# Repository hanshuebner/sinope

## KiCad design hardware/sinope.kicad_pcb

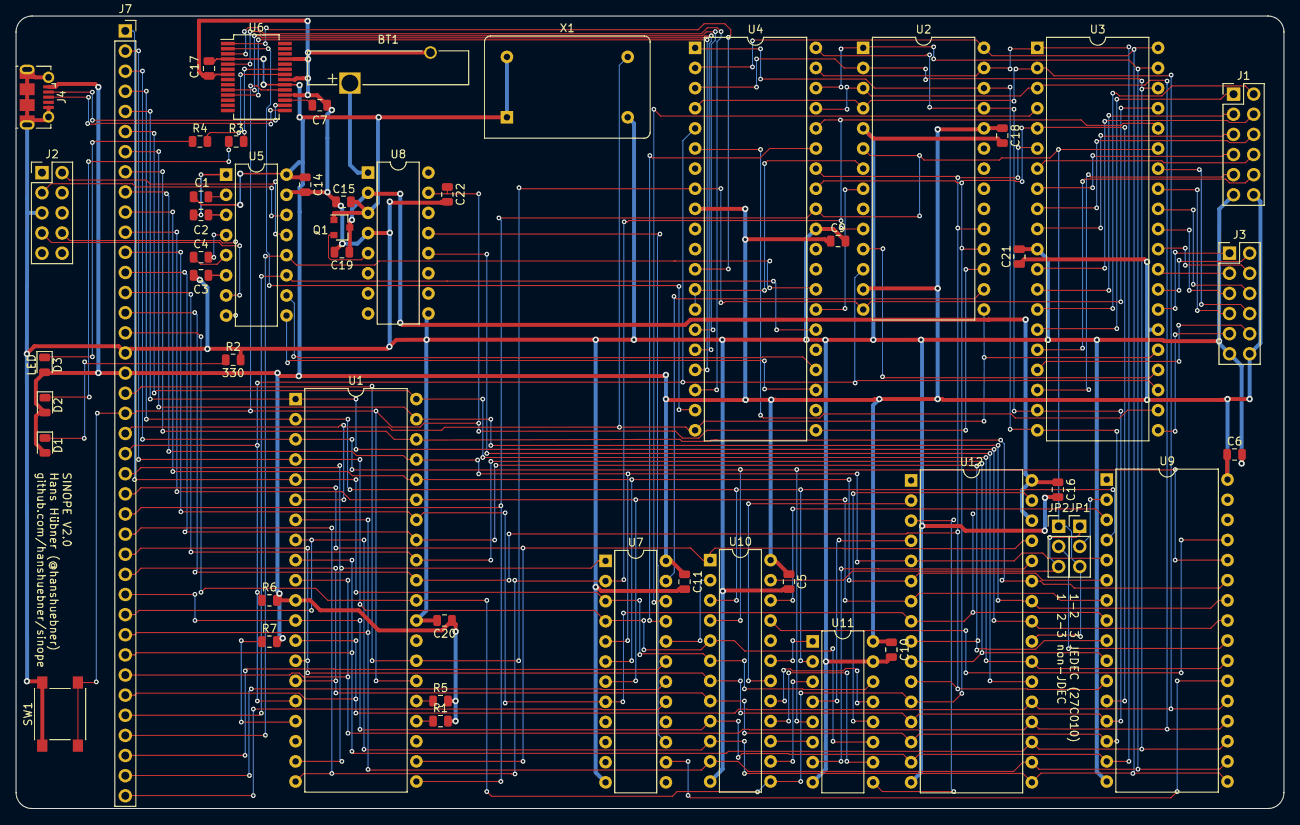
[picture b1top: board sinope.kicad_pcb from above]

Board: 2 copper layers, 160.0 x 100.0 mm, 52 parts (0 on the bottom side), 117 nets.

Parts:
BT1: Battery; Battery_Panasonic_CR2032-VS1N_Vertical_CircularHoles
C1, C2, C3, C4, C5, C6, C7, C9, C10, C11, C14, C15, C16, C17, C18, C19, C20, C21, C22: 100nF; C_0805_2012Metric
D1, D2, D3: LED; LED_0805_2012Metric
J1: PIOA; PinHeader_2x06_P2.54mm_Vertical
J2: SERIAL1; PinHeader_2x05_P2.54mm_Vertical
J3: PIOB; PinHeader_2x06_P2.54mm_Vertical
J4: USB_B_Micro; USB_Micro-B_Molex-105017-0001
J7: Z80_BUS; PinSocket_1x39_P2.54mm_Vertical
JP1, JP2: SolderJumper_3_Bridged12; PinHeader_1x03_P2.54mm_Vertical
Q1: MMBT3904; SOT-23
R1, R5, R6, R7: 3k3; R_0805_2012Metric
R2, R3, R4: 330; R_0805_2012Metric
SW1: RESET; SW_SPST_PTS645
U1: Z80CPU; DIP-40_W15.24mm
U2: Z80CTC; DIP-28_W15.24mm
U3: Z80PIO; DIP-40_W15.24mm
U4: Z80SIO; DIP-40_W15.24mm
U5: MAX232; DIP-16_W7.62mm
U6: FT232RL; SSOP-28_5.3x10.2mm_P0.65mm
U7: IO_GAL; DIP-24_W7.62mm
U8: MAX695; DIP-16_W7.62mm
U9: 27C010; DIP-32_W15.24mm
U10: MEMORY_GAL; DIP-24_W7.62mm
U11: 74LS157; DIP-16_W7.62mm
U12: TC551001; DIP-32_W15.24mm
X1: 3.6864Mhz; Oscillator_DIP-14

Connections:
+5V: C1.2, C5.1, C6.1, C9.1, C10.1, C11.1, C14.1, C15.1, C17.1, C18.1, C20.1, C21.1, D1.2, D2.2, D3.2, J1.12, J3.12, J4.1, J7.18, Q1.1, R1.2, R5.2, R6.2, R7.2, U1.11, U2.13, U2.24, U3.26, U4.9, U5.16, U6.4, U6.20, U7.24, U8.3, U9.32, U10.24, U11.16, X1.1, X1.14
/A0: J7.16, U1.30, U2.18, U3.5, U4.33, U9.12, U10.13, U12.12
/A1: J7.15, U1.31, U2.19, U3.6, U4.34, U9.11, U12.11
/A2: J7.14, U1.32, U9.10, U12.10
/A3: J7.13, U1.33, U9.9, U12.9
/A4: J7.12, U1.34, U7.8, U9.8, U12.8
/A5: J7.11, U1.35, U7.7, U9.7, U12.7
/A6: J7.10, U1.36, U7.6, U9.6, U12.6
/A7: J7.9, U1.37, U7.5, U9.5, U12.5
/A8: J7.8, U1.38, U9.27, U12.27
/A9: J7.7, U1.39, U9.26, U12.26
/A10: J7.6, U1.40, U9.23, U12.23
/A11: J7.5, U1.1, U9.25, U12.25
/A12: J7.4, U1.2, U9.4, U10.3, U11.2
/A13: J7.3, U1.3, U9.28, U10.4, U11.5
/A14: J7.2, U1.4, U7.4, U10.5, U11.11
/A15: J7.1, U1.5, U7.3, U10.6, U11.14
/D0: J7.27, U1.14, U2.25, U3.19, U4.40, U9.13, U10.7, U12.13
/D1: J7.28, U1.15, U2.26, U3.20, U4.1, U9.14, U10.8, U12.14
/D2: J7.29, U1.12, U2.27, U3.1, U4.39, U9.15, U10.9, U12.15
/D3: J7.30, U1.8, U2.28, U3.40, U4.2, U9.17, U10.10, U12.17
/D4: J7.31, U1.7, U2.1, U3.39, U4.38, U9.18, U10.11, U12.18
/D5: J7.32, U1.9, U2.2, U3.38, U4.3, U9.19, U12.19
/D6: J7.33, U1.10, U2.3, U3.3, U4.37, U9.20, U12.20
/D7: J7.34, U1.13, U2.4, U3.2, U4.4, U9.21, U12.21
/ROMA14: U9.29, U10.21
/ROMA15: U9.3, U10.22
/ROMA16: JP1.1, JP2.3, U10.23
CLK: J7.21, U1.6, U2.15, U3.25, U4.20, X1.8
GND: BT1.2, C3.1, C5.2, C6.2, C7.2, C9.2, C10.2, C11.2, C14.2, C15.2, C16.2, C17.2, C18.2, C19.2, C20.2, C21.2, C22.2, J1.11, J2.5, J3.11, J4.5, J4.6, J7.17, R2.2, SW1.1, U1.29, U2.5, U3.11, U4.31, U5.15, U6.7, U6.18, U6.21, U6.25, U7.12, U8.4, U8.9, U9.16, U10.12, U11.8, U11.15, U12.16, X1.7
unnamed: BT1.1, U8.1
unnamed: C1.1, U5.2
unnamed: C2.1, U5.1
unnamed: C2.2, U5.3
unnamed: C3.2, U5.6
unnamed: C4.1, U5.5
unnamed: C4.2, U5.4
unnamed: C7.1, U6.17
unnamed: D1.1, R2.1
unnamed: D2.1, R3.1
unnamed: D3.1, R4.1
unnamed: J1.1, U3.15
unnamed: J1.2, U3.14
unnamed: J1.3, U3.13
unnamed: J1.4, U3.12
unnamed: J1.5, U3.10
unnamed: J1.6, U3.9
unnamed: J1.7, U3.8
unnamed: J1.8, U3.7
unnamed: J1.9, U3.18
unnamed: J1.10, U3.16
unnamed: J2.2, U5.13
unnamed: J2.3, U5.14
unnamed: J2.7, U5.7
unnamed: J2.8, U5.8
unnamed: J3.1, U3.27
unnamed: J3.2, U3.28
unnamed: J3.3, U3.29
unnamed: J3.4, U3.30
unnamed: J3.5, U3.31
unnamed: J3.6, U3.32
unnamed: J3.7, U3.33
unnamed: J3.8, U3.34
unnamed: J3.9, U3.21
unnamed: J3.10, U3.17
unnamed: JP1.2, U9.2
unnamed: JP2.2, U9.24
unnamed: Q1.2, U8.5
unnamed: R3.2, U6.23
unnamed: R4.2, U6.22
unnamed: U2.11, U3.24
unnamed: U3.22, U4.6
unnamed: U4.12, U6.1
unnamed: U4.15, U6.5
unnamed: U4.16, U6.10
unnamed: U4.17, U6.11
unnamed: U4.18, U6.3
unnamed: U4.19, U6.2
unnamed: U4.23, U5.9
unnamed: U4.24, U5.10
unnamed: U10.14, U11.3
unnamed: U10.15, U11.6
unnamed: U10.16, U11.10
unnamed: U10.17, U11.13
unnamed: U10.19, U11.1
unnamed: U11.4, U12.4
unnamed: U11.7, U12.28
unnamed: U11.9, U12.3
unnamed: U11.12, U12.31
RAMA16: U10.18, U12.2
RAMVCC: C16.1, C19.1, Q1.3, U8.2, U12.30, U12.32
RxDB: J7.36, U4.28, U5.12
SIOCA: U2.7, U4.13, U4.14
SIOCB: U2.8, U4.27
SPARE1: J7.37, U7.19
SPARE2: J7.38, U7.18
SPARE3: J7.39, U7.17
TxDB: J7.35, U4.26, U5.11
USB_D+: J4.3, U6.15
USB_D-: J4.2, U6.16
~BANKCS: U7.20, U10.2
~BUSRQ: R5.1, U1.25
~CTCCS: U2.16, U7.23
~INT: J7.22, R6.1, U1.16, U2.12, U3.23, U4.5
~IOREQ: J7.26, U1.20, U2.10, U3.36, U4.36, U7.2
~M1: J7.19, U1.27, U2.14, U3.37, U4.8
~MREQ: J7.23, U1.19, U7.1
~NMI: R7.1, U1.17
~PIOCS: U3.4, U7.22
~RAMCS: U7.15, U8.13
~RAMCS_SAFE: U8.12, U12.22
~RD: J7.25, JP1.3, JP2.1, U1.21, U2.6, U3.35, U4.32, U12.24
~RESET: C22.1, J7.20, SW1.2, U1.26, U2.17, U4.21, U6.19, U8.15
~ROMCS: U7.14, U9.22
~SIOCS: U4.35, U7.21
~WAIT: R1.1, U1.24
~WR: J7.24, U1.22, U10.1, U12.29

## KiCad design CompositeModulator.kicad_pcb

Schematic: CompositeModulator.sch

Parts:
C23, C44: 10uF
C24, C26: 10pF
C25, C28, C30, C34, C45: 1nF
C27: 150pF
C29: 13pF
C31: 47pF
C32: 100µF
C33: 56pF
C35, C37, C41: 100pF
C36: 7pF
C38, C40: 680pF
C39: 6-50pF
C42: 100nF; C_0805_2012Metric
C43: 390pF
L1, L2: 3.9µH
L3: 1.35-2.25µH
Q2: 9015
Q3: 9014
R3, R9, R10, R16, R21, R22: 560
R4: 47k
R5: 680
R6: 2.7k
R7: 820
R8: 5.6k
R11, R17: 10k
R12, R13, R18: 2.2k
R14: 220
R15: 270
R19, R20: 390
U13: TBA520
U14: 74LS04
Y1: 4.433618 Mhz

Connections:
+5V: C42.1, L2.1, Q2.1 (E), R11.1, R17.1, U13.6; also elsewhere on the board
GND: C25.2, C27.2, C28.2, C31.2, C32.2, C33.2, C34.2, C41.2, C42.2, C43.2, C44.2, C45.2, L3.2, R3.2, R4.2, R5.2, R9.2, R11.3, R13.2, R14.2, R16.2, R17.3, R19.2, U13.16; also elsewhere on the board
unnamed 2: C23.1, C25.1, L1.1, R3.1; also elsewhere on the board
unnamed: C23.2, Q2.2 (B), R4.1
unnamed: C24.1, U13.15
unnamed: C24.2, C26.2, Q2.3 (C), R5.1
unnamed: C26.1, U13.14
unnamed: C27.1, L1.2, R6.1
unnamed 8: C28.1, R7.2, R9.1; also elsewhere on the board
unnamed: C29.1, R10.2
unnamed: C29.2, C30.1, U13.5
unnamed: C30.2, C33.1, L3.1, R13.1
unnamed: C31.1, C32.1, L2.2, Q3.3, R8.1
unnamed 13: C34.1, C35.2, R15.2, R16.1; also elsewhere on the board
unnamed: C35.1, R15.1, R18.2, U13.13
unnamed: C36.1, C37.2, R20.2
unnamed: C36.2, C39.1, Y1.1
unnamed: C37.1, C38.2, R19.1
unnamed: C38.1, U13.2
unnamed: C39.2, C43.1, R21.2, U14.1
unnamed: C40.1, U13.8
unnamed: C40.2, C41.1, R20.1
unnamed: C44.1, R21.1, R22.2
unnamed: C45.1, R22.1, U14.2, Y1.2
unnamed 24: Q3.1, R14.1; also elsewhere on the board
unnamed: Q3.2, R6.2, R8.2, R10.1
unnamed: R11.2, R12.1
unnamed: R7.1, R12.2, U13.9
unnamed: R17.2, R18.1

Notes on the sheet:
(Q=100)
(Q=130)
This is a reproduction of the SVI328 video modulator circuitry
from http://www.samdal.com/SVIDOCS/STM-A_SVI328.pdf page 21

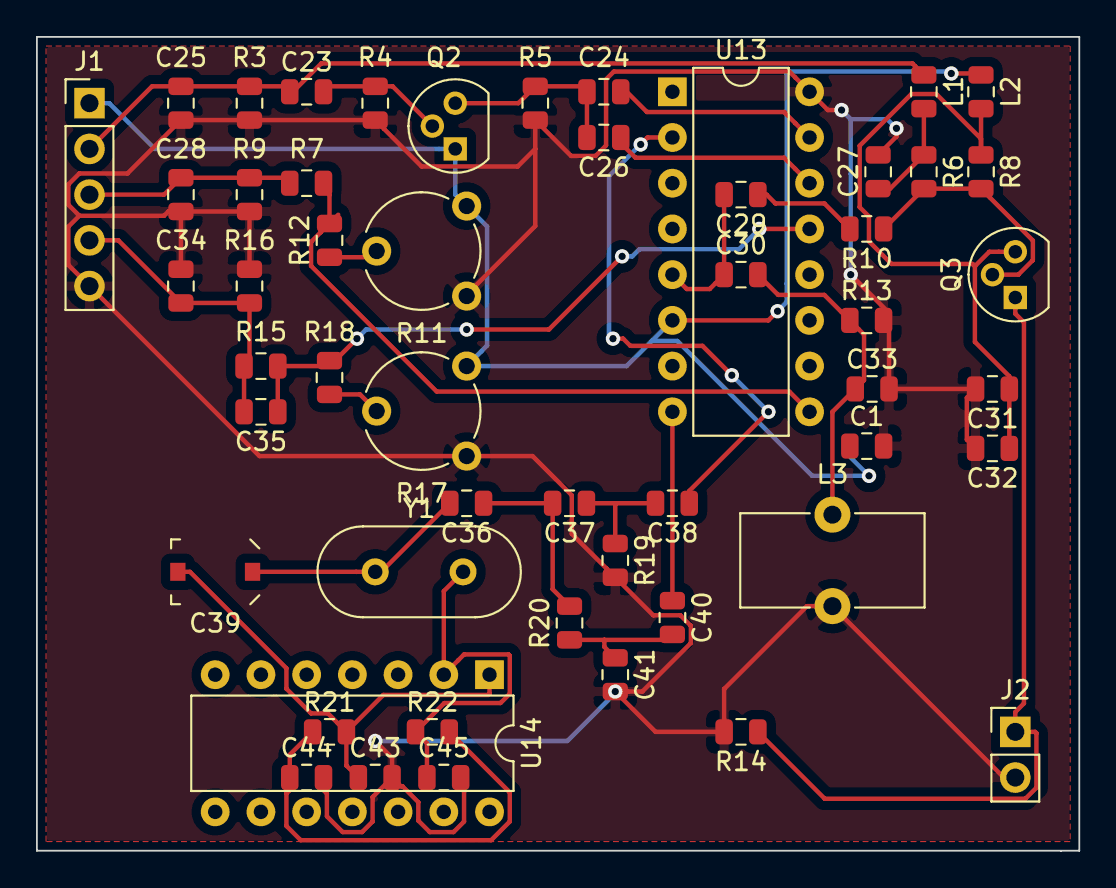
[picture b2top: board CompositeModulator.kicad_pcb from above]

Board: 2 copper layers, 57.9 x 45.2 mm, 53 parts (0 on the bottom side), 29 nets.

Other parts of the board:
C1: 100nF; C_0805_2012Metric
J1: Input; PinHeader_1x05_P2.54mm_Vertical
J2: Composite Video; PinHeader_1x02_P2.54mm_Vertical

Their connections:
+5V: C1.1, J1.1; also elsewhere on the board
GND: C1.2, J1.5, J2.2; also elsewhere on the board
unnamed 2: J1.2; also elsewhere on the board
unnamed 8: J1.3; also elsewhere on the board
unnamed 13: J1.4; also elsewhere on the board
unnamed 24: J2.1; also elsewhere on the board

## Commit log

2020-04-13 .gitignore
2020-04-13 SRAM Battery Backup
2020-04-13 Video interface
2020-04-15 Rip out graphics
2020-04-15 Add GAL configuration
2020-04-15 Reassemble GAL code
2020-04-15 More GAL experimentation
2020-04-15 Try fixing GAL logic
2020-04-15 Address decoding tested to work
2020-04-15 Address decoding works, Makefile
2020-04-15 Use integrated oscillator
2020-04-16 Touchup
2020-04-17 Memory management logic
2020-04-17 Banking logic documentation update
2020-04-17 Package assignments, PCB work
2020-04-18 Add composite modulator for TMS9929A
2020-04-18 Add sheet labels
2020-04-18 Remove composite modulator from sheet label for now
2020-04-18 Add composite modulator PCB as test project
2020-04-20 PCB mostly routed
2020-04-20 PCB work
2020-04-20 PCB routed
2020-04-20 Add gerber files
2020-04-20 Move connectors to one side.
2020-04-20 ROM variant jumpers and cleanup, sent to JLCPCB for production
2020-04-29 Begin work on v2
2020-04-29 Reorganize
2020-04-29 Layout redone quickly
2020-05-01 Layout improved
2022-05-08 Add new files
2022-05-08 Make it match the actual build
2022-05-09 Add hardware test program
2022-05-09 Ignore binary
2022-05-09 Fix port addresses
2022-05-09 Replace connectors to reflect reality
2022-05-09 Display multiplex test
2022-05-09 Cleanup
2022-05-10 fix nibble order
2022-05-10 Try SIO initialization
2022-05-15 Working up counter
2022-05-15 Can process CTC interrupts
2022-05-15 Display control by CTC ISR
2022-05-15 Counter controlled by PIO input
2022-05-15 Can say hello on SIO
2022-05-16 Generates PIO interrupts
2022-05-16 Encoder port, status led, reset tweaks, PIO reset
